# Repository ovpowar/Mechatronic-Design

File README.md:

# Mechatronic-Design
Repo for Mechatronic Design Codes

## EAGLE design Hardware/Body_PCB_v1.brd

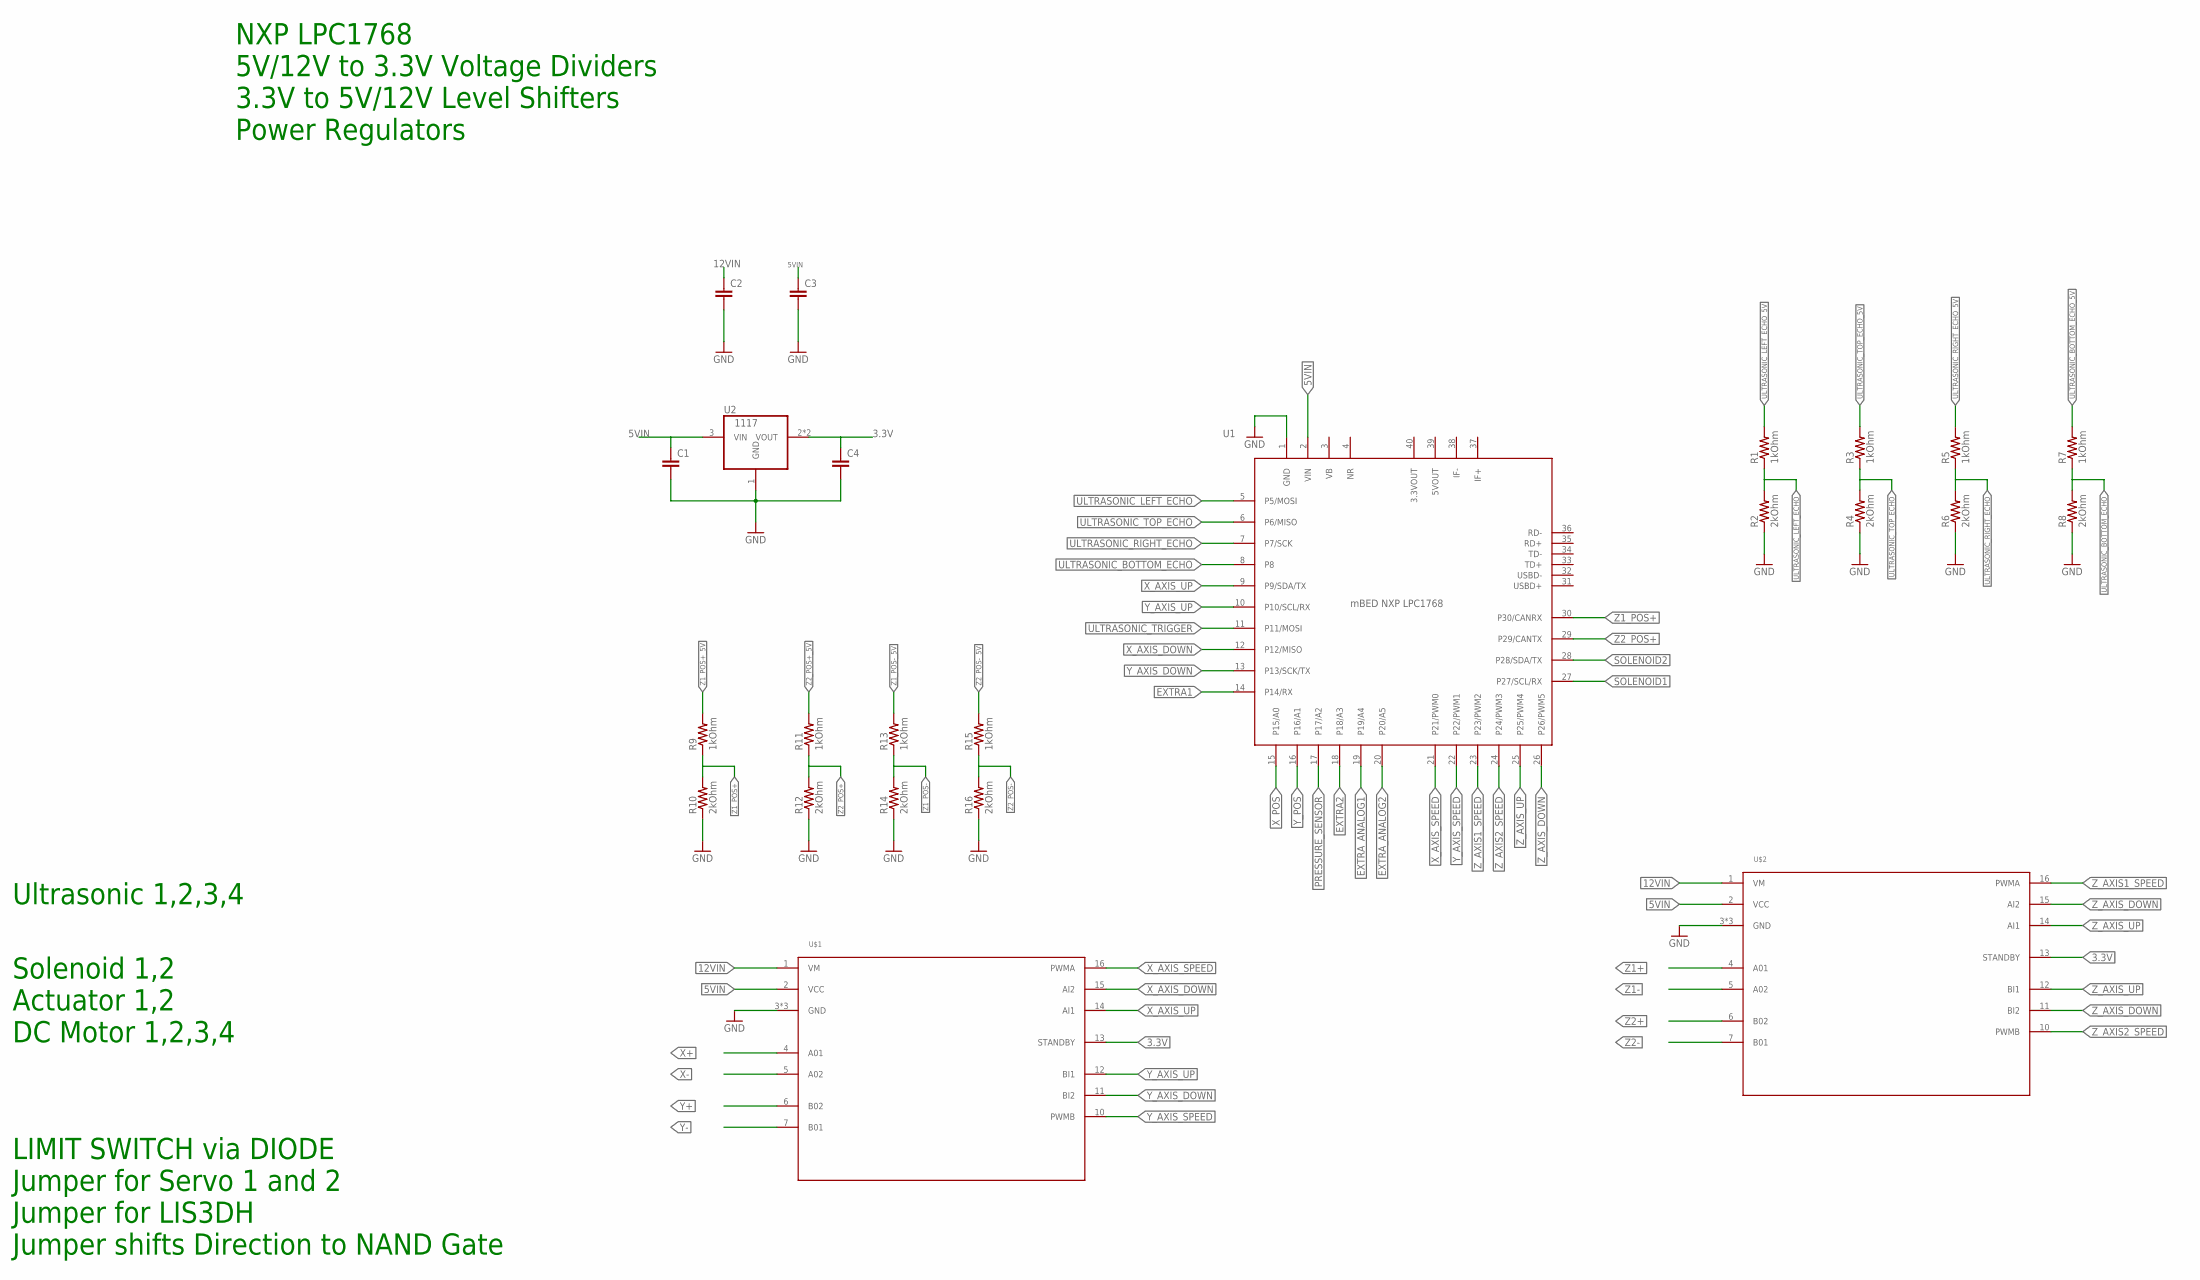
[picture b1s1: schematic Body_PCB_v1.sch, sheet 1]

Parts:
C1, C2, C3, C4: C1206; 1206
R1, R3, R5, R7, R9, R11, R13, R15: 1kOhm; 0805
R2, R4, R6, R8, R10, R12, R14, R16: 2kOhm; 0805
U1: MBED_NXP_LPC1768; 40_PDIP
U2: 1117; SOT223
U$1, U$2: TB6612FNG; TB6612FNG_DRIVER

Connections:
3.3V: C4.1, U2.2 (VOUT), U2.4 (VOUT), U$1.13 (STANDBY), U$2.13 (STANDBY); also elsewhere on the board
5VIN: C1.1, C3.1, U1.2 (VIN), U2.3 (VIN), U$1.2 (VCC), U$2.2 (VCC); also elsewhere on the board
12VIN: C2.1, U$1.1 (VM), U$2.1 (VM); also elsewhere on the board
EXTRA1: U1.14 (P14/RX); also elsewhere on the board
EXTRA2: U1.18 (P18/A3); also elsewhere on the board
EXTRA_ANALOG1: U1.19 (P19/A4)
EXTRA_ANALOG2: U1.20 (P20/A5)
GND: C1.2, C2.2, C3.2, C4.2, R2.P$1 (1), R4.P$1 (1), R6.P$1 (1), R8.P$1 (1), R10.P$1 (1), R12.P$1 (1), R14.P$1 (1), R16.P$1 (1), U1.1 (GND), U2.1 (GND), U$1.3 (GND), U$1.8 (GND), U$1.9 (GND), U$2.3 (GND), U$2.8 (GND), U$2.9 (GND); also elsewhere on the board
PRESSURE_SENSOR: U1.17 (P17/A2)
SOLENOID1: U1.27 (P27/SCL/RX); also elsewhere on the board
SOLENOID2: U1.28 (P28/SDA/TX); also elsewhere on the board
ULTRASONIC_BOTTOM_ECHO: R7.P$1 (1), R8.P$2 (2), U1.8
ULTRASONIC_BOTTOM_ECHO_5V: R7.P$2 (2); also elsewhere on the board
ULTRASONIC_LEFT_ECHO: R1.P$1 (1), R2.P$2 (2), U1.5 (P5/MOSI)
ULTRASONIC_LEFT_ECHO_5V: R1.P$2 (2); also elsewhere on the board
ULTRASONIC_RIGHT_ECHO: R5.P$1 (1), R6.P$2 (2), U1.7 (P7/SCK)
ULTRASONIC_RIGHT_ECHO_5V: R5.P$2 (2); also elsewhere on the board
ULTRASONIC_TOP_ECHO: R3.P$1 (1), R4.P$2 (2), U1.6 (P6/MISO)
ULTRASONIC_TOP_ECHO_5V: R3.P$2 (2); also elsewhere on the board
ULTRASONIC_TRIGGER: U1.11 (P11/MOSI); also elsewhere on the board
X+: U$1.4 (A01); also elsewhere on the board
X-: U$1.5 (A02); also elsewhere on the board
X_AXIS_DOWN: U1.12 (P12/MISO), U$1.15 (AI2)
X_AXIS_SPEED: U1.21 (P21/PWM0), U$1.16 (PWMA)
X_AXIS_UP: U1.9 (P9/SDA/TX), U$1.14 (AI1)
X_POS: U1.15 (P15/A0); also elsewhere on the board
Y+: U$1.6 (B02); also elsewhere on the board
Y-: U$1.7 (B01); also elsewhere on the board
Y_AXIS_DOWN: U1.13 (P13/SCK/TX), U$1.11 (BI2)
Y_AXIS_SPEED: U1.22 (P22/PWM1), U$1.10 (PWMB)
Y_AXIS_UP: U1.10 (P10/SCL/RX), U$1.12 (BI1)
Y_POS: U1.16 (P16/A1); also elsewhere on the board
Z1+: U$2.4 (A01); also elsewhere on the board
Z1-: U$2.5 (A02); also elsewhere on the board
Z1_POS+: R9.P$1 (1), R10.P$2 (2), U1.30 (P30/CANRX)
Z1_POS+_5V: R9.P$2 (2); also elsewhere on the board
Z1_POS-: R13.P$1 (1), R14.P$2 (2); also elsewhere on the board
Z1_POS-_5V: R13.P$2 (2); also elsewhere on the board
Z2+: U$2.6 (B02); also elsewhere on the board
Z2-: U$2.7 (B01); also elsewhere on the board
Z2_POS+: R11.P$1 (1), R12.P$2 (2), U1.29 (P29/CANTX)
Z2_POS+_5V: R11.P$2 (2); also elsewhere on the board
Z2_POS-: R15.P$1 (1), R16.P$2 (2); also elsewhere on the board
Z2_POS-_5V: R15.P$2 (2); also elsewhere on the board
Z_AXIS1_SPEED: U1.23 (P23/PWM2), U$2.16 (PWMA)
Z_AXIS2_SPEED: U1.24 (P24/PWM3), U$2.10 (PWMB)
Z_AXIS_DOWN: U1.26 (P26/PWM5), U$2.11 (BI2), U$2.15 (AI2)
Z_AXIS_UP: U1.25 (P25/PWM4), U$2.12 (BI1), U$2.14 (AI1)

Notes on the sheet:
NXP LPC1768 5V/12V to 3.3V Voltage Dividers 3.3V to 5V/12V Level Shifters Power Regulators
Ultrasonic 1,2,3,4
Solenoid 1,2 Actuator 1,2 DC Motor 1,2,3,4
LIMIT SWITCH via DIODE Jumper for Servo 1 and 2 Jumper for LIS3DH Jumper shifts Direction to NAND Gate

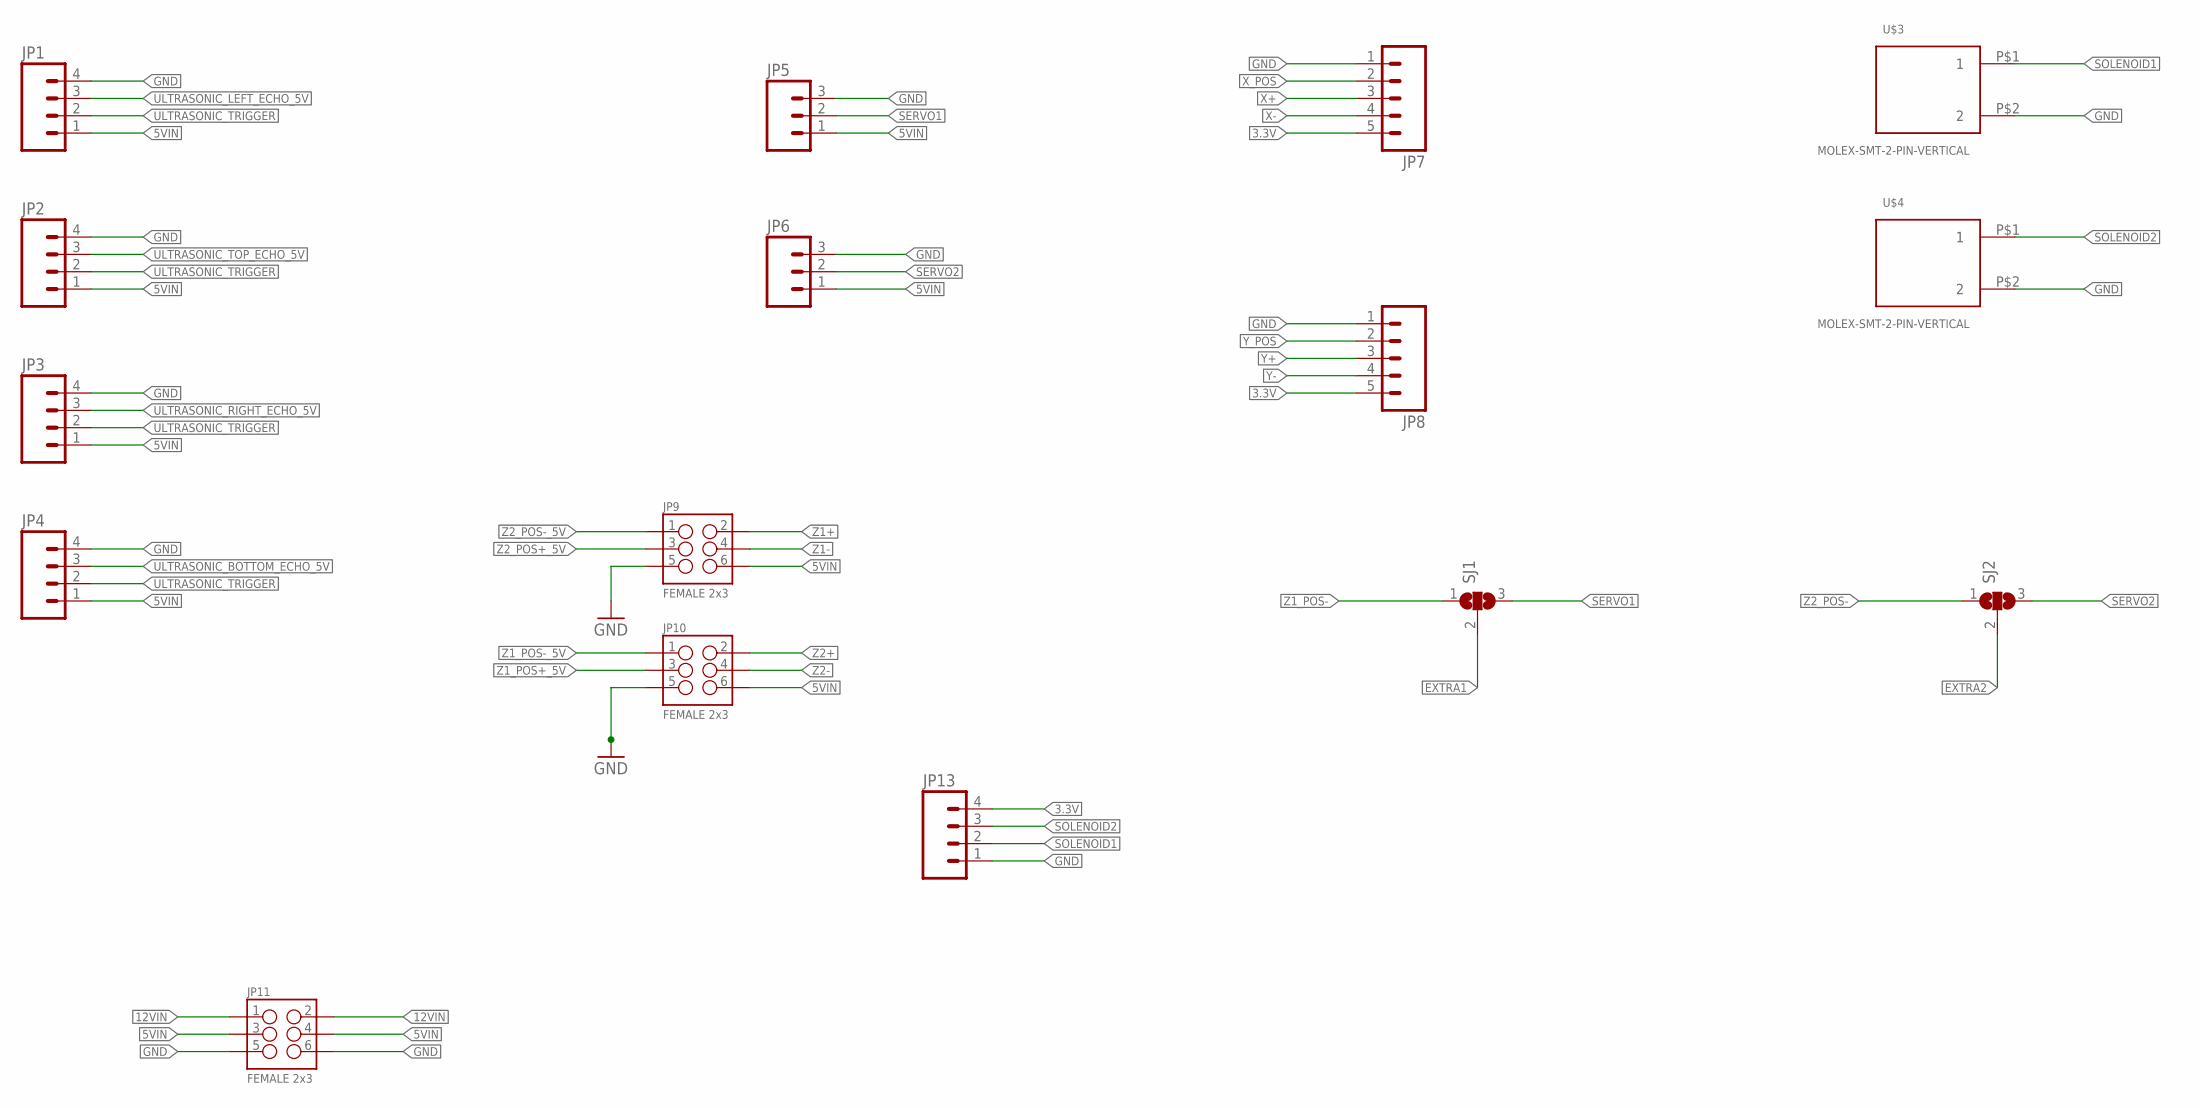
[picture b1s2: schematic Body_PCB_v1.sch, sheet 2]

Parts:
JP1, JP2, JP3, JP4, JP13: M04PTH; 1X04
JP5, JP6: M03PTH; 1X03
JP7, JP8: M05PTH; 1X05
JP9, JP10, JP11: FEMALE 2x3; 2X3
SJ1, SJ2: SJ2W; SJ_2
U$3, U$4: MOLEX-SMT-2-PIN-VERTICAL; 430450215

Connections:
3.3V: JP7.5, JP8.5, JP13.4; also elsewhere on the board
5VIN: JP1.1, JP2.1, JP3.1, JP4.1, JP5.1, JP6.1, JP9.6, JP10.6, JP11.3, JP11.4; also elsewhere on the board
12VIN: JP11.1, JP11.2; also elsewhere on the board
EXTRA1: SJ1.2; also elsewhere on the board
EXTRA2: SJ2.2; also elsewhere on the board
GND: JP1.4, JP2.4, JP3.4, JP4.4, JP5.3, JP6.3, JP7.1, JP8.1, JP9.5, JP10.5, JP11.5, JP11.6, JP13.1, U$3.P$2 (2), U$4.P$2 (2); also elsewhere on the board
SERVO1: JP5.2, SJ1.3
SERVO2: JP6.2, SJ2.3
SOLENOID1: JP13.2, U$3.P$1 (1); also elsewhere on the board
SOLENOID2: JP13.3, U$4.P$1 (1); also elsewhere on the board
ULTRASONIC_BOTTOM_ECHO_5V: JP4.3; also elsewhere on the board
ULTRASONIC_LEFT_ECHO_5V: JP1.3; also elsewhere on the board
ULTRASONIC_RIGHT_ECHO_5V: JP3.3; also elsewhere on the board
ULTRASONIC_TOP_ECHO_5V: JP2.3; also elsewhere on the board
ULTRASONIC_TRIGGER: JP1.2, JP2.2, JP3.2, JP4.2; also elsewhere on the board
X+: JP7.3; also elsewhere on the board
X-: JP7.4; also elsewhere on the board
X_POS: JP7.2; also elsewhere on the board
Y+: JP8.3; also elsewhere on the board
Y-: JP8.4; also elsewhere on the board
Y_POS: JP8.2; also elsewhere on the board
Z1+: JP9.2; also elsewhere on the board
Z1-: JP9.4; also elsewhere on the board
Z1_POS+_5V: JP10.3; also elsewhere on the board
Z1_POS-: SJ1.1; also elsewhere on the board
Z1_POS-_5V: JP10.1; also elsewhere on the board
Z2+: JP10.2; also elsewhere on the board
Z2-: JP10.4; also elsewhere on the board
Z2_POS+_5V: JP9.3; also elsewhere on the board
Z2_POS-: SJ2.1; also elsewhere on the board
Z2_POS-_5V: JP9.1; also elsewhere on the board

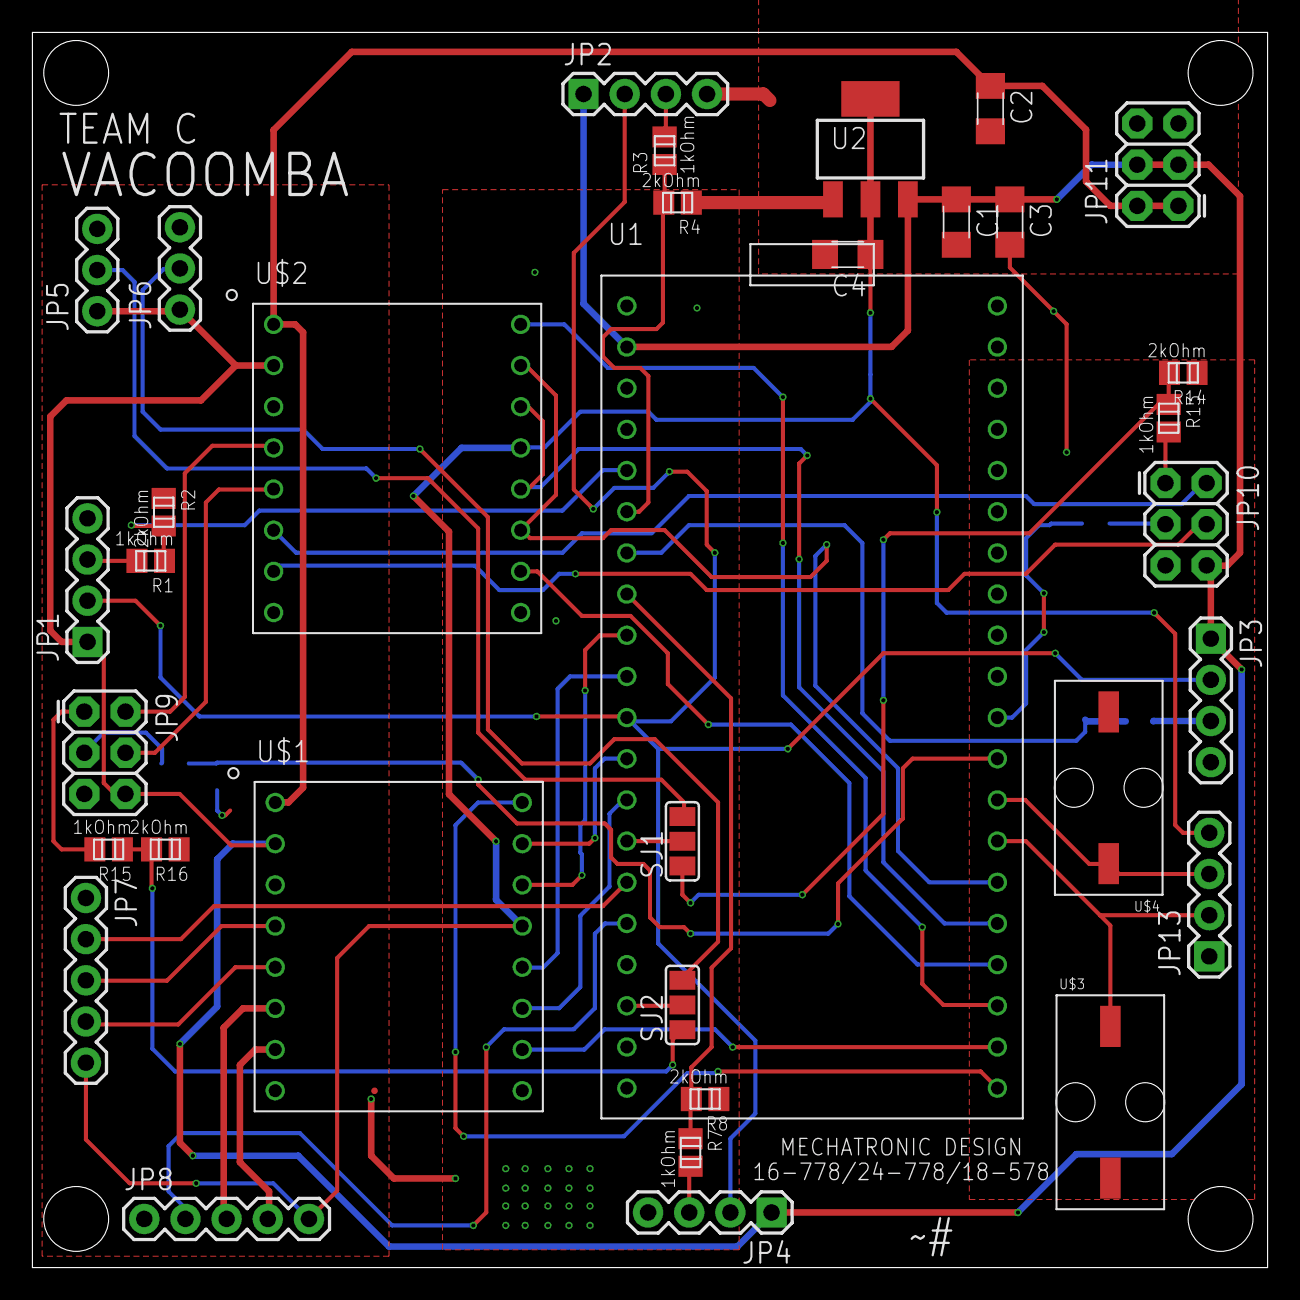
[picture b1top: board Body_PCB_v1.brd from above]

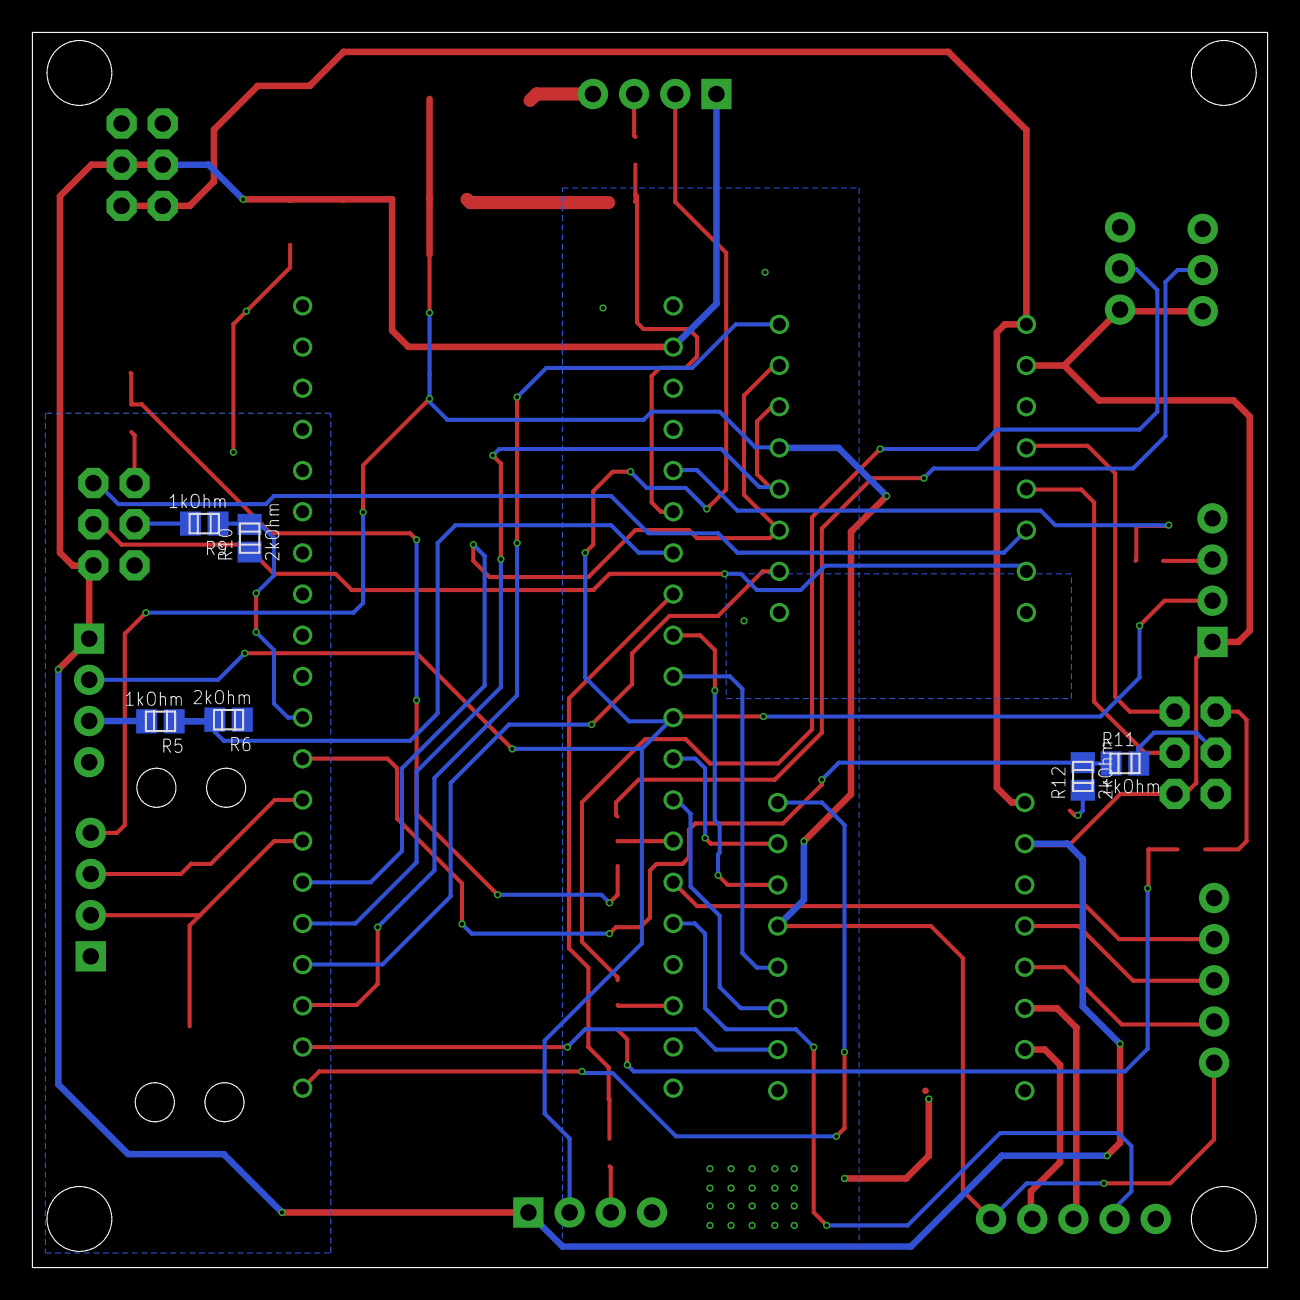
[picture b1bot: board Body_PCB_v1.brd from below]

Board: 2 copper layers, 76.2 x 76.2 mm, 40 parts (6 on the bottom side), 47 nets.

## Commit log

2019-02-16 Transfer of Files from Local System
    `Transferring all Code files for the project to the repo
2019-02-18 Create Rotary_Linear_Code.ino
    Rotary Linear Test Code Added
    - Virtual Limit Switching
    - 0 to stop
    - 1 to move in
    - 2 to move out
2019-02-24 Linear Actuator
    - Added Code for Linear Actuator
    - Updated code for inchworming
2019-02-25 Created PID_Test.ino
    - PID Test code found online
2019-03-31 2D Inchowrming on Flat Surface
    - Added Inchworming Codes
    - Changed path for all Arduino Files
2019-04-03 Addition of 2D Vertical Surface Code
    - Added code for Vertical Steps
    - No feedback from Z Axis motors
    - Andrew. This is for you.

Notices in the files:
parts and their libraries:
SparkFun-Connectors: Licensing: CC v3.0 Share-Alike You are welcome to use this library for commercial purposes.
SparkFun-Boards: Licensing: Creative Commons ShareAlike 4.0 International - https://creativecommons.org/licenses/by-sa/4.0
